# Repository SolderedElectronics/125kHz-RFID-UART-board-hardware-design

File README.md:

# 125kHz RFID tag reader UART board Hardware Design

## About the Product

|  |
| :----------------------------------------------------------: |
| [Buy 125kHz RFID tag reader UART board](https://www.solde.red/333154) |

RFID is a type of communication in which information is transmitted wirelessly (Wikipedia article). Today, it is becoming increasingly popular and can be found in numerous and various cards: driving licenses, access control to buildings, public transportation, etc.

RFID readers come in many forms and variants. This reader, from our production, enables easy connection to a microcontroller, thereby opening up possibilities for developing various projects based on RFID technology. The breakout comes in two versions, and depending on the version, it is programmed and ready for communication via pins on the board. It has a switch for changing the data transfer speed (baud rate) as well as a connector for connecting the antenna that comes with the breakout.

---

## Repository Contents

This repository contains all design files for 125kHz RFID tag reader UART board, organized as follows:

- **`CAD` folder**: Contains KiCAD design files, including:
  - Schematics
  - PCB layout
  - Panel PCB layout
  - Source 3D files in Fusion360, if any
  - All files are sorted by version with a detailed change log.
- **`OUTPUTS` folder**: Includes all production-ready files, such as:
  - Bill of Materials (BOM) and interactive BOM (iBOM)
  - PDF versions of schematics
  - 3D `.step` file of the board
  - 3D-printable models
  - Gerber files for PCB manufacturing
  - Image of the pinout of the board
  - Product image
  - Compliance, legal and generic sales documents

Refer to the `Change Log` in the CAD folder for details about updates between versions.

---

## Learn More About the Product

Beyond the repository, explore the following resources:

### Soldered Verify

The **Soldered Verify** system ensures every board you purchase from Soldered is fully functional. It also provides access to exclusive test data for your product. To get started, find the unique Soldered Verify ID on your product's packaging and enter the ID on the [Soldered Verify page](https://soldered.com/verify/) to access test results and additional product details.

### Soldered Community

Soldered Community is your go-to place for technical support. Our engineers track and answer all questions posted there, and it’s a great space for the maker community. Get answers to your questions and solutions for your challenges at [Soldered Community](https://soldered.com/community).

### solde.red

solde.red is an ultimate URL shortener and information hub. Access it by typing solde.red/ followed by your product SKU, e.g., [solde.red/333000](https://solde.red/333000), to find getting-started guides, datasheets, open-source hardware and software files, certifications, images, pinouts, and more. Read more about the shortener [here](https://solde.red/info/).

---

## Contributing

Contributions are welcome! Here’s how you can get involved:

- Submit pull requests to enhance the design or fix issues.
- Report bugs or problems by opening an issue.

We encourage community collaboration to make this product even better.

---

## About Soldered

[Soldered for Makers](https://soldered.com) specializes in designing and manufacturing electronic products tailored for enthusiasts, ranging from hobbyists to professionals. Our portfolio includes electronic boards, sensors, and actuators that are widely utilized in fields such as microelectronics, mechatronics, robotics, programming, and IoT. Every product we offer is designed in-house and built upon open-source hardware and software platforms. Proudly certified and manufactured within the European Union, our catalog likely includes the product you need for your project.

We complement these products with comprehensive tutorials and manuals, product descriptions, schematics, programming codes, and project examples. Our round-the-clock [customer and technical support](https://soldered.com/community) is available for all our products, irrespective of the sales channel. Soldered’s success and services reflect our maker community’s unwavering [trust](https://www.trustpilot.com/review/soldered.com), for which we are deeply grateful. Join our community and create using Soldered products.

---

## License

All Soldered open-source hardware (OSH) is under The TAPR Open Hardware License. Read more in the LICENSE file located in this repository.

**Disclaimer:**

No warranty - all designs in this repository are distributed in the hope that they will be useful, but without any warranty. They are provided "AS IS", therefore without warranty of any kind, either expressed or implied. The entire quality and performance of what you do with the contents of this repository are your responsibility. In no event Soldered Electronics will be liable for your damages, or losses, including any general, special, incidental, or consequential damage arising out of the use or inability to use the contents of this repository. 

---

## Have fun!

Thank you for your support from your fellow makers at Soldered Electronics.

Happy Making!

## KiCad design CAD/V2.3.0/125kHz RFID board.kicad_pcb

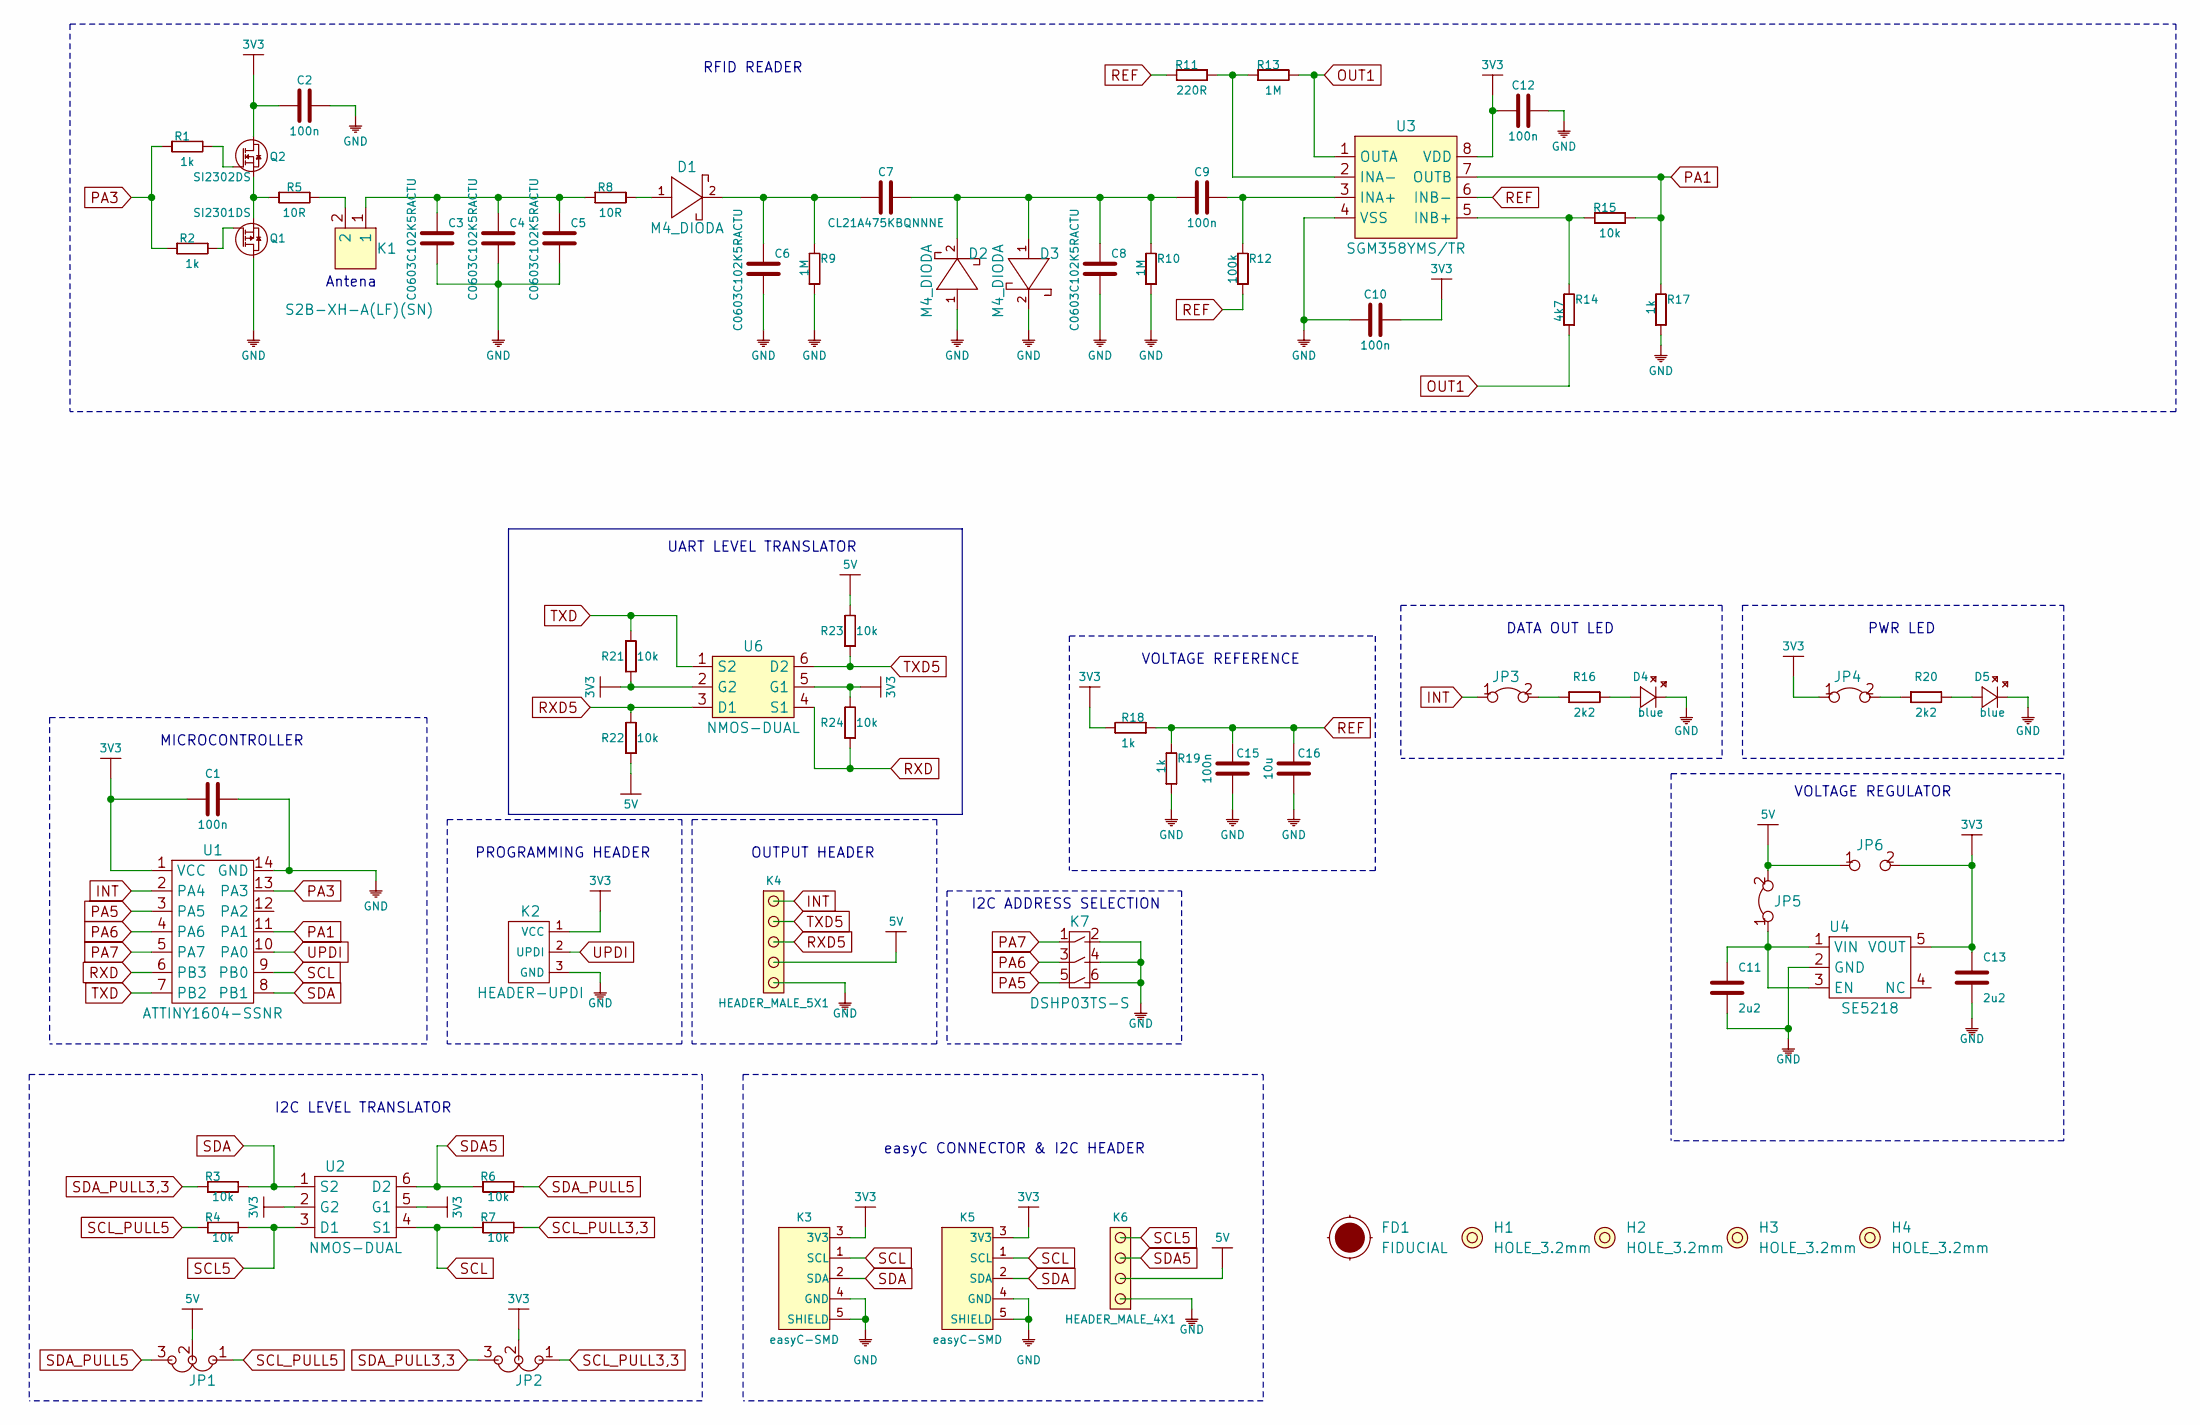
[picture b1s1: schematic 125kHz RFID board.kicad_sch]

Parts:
C1, C2, C9, C10, C12, C15: 100n; 0603C
C3, C4, C5, C6, C8: C0603C102K5RACTU; 0603C
C7: CL21A475KBQNNNE; 0805C
C11, C13: 2u2; 0603C
C16: 10u; 1206C
D1, D2, D3: M4_DIODA
D4, D5: blue; 0402LED
FD1: FIDUCIAL; FIDUCIAL_23
H1, H2, H3, H4: HOLE_3.2mm
JP1, JP2: SMD_JUMPER_3_PAD_TRACE
JP3, JP4: SMD-JUMPER-CONNECTED_TRACE_SLODERMASK
JP5: SMD-JUMPER-CONNECTED_TRACE_SOLDERMASK
JP6: SMD_JUMPER
K1: S2B-XH-A(LF)(SN)
K2: HEADER-UPDI
K3, K5: easyC-SMD; easyC-connector
K4: HEADER_MALE_5X1
K6: HEADER_MALE_4X1
K7: DSHP03TS-S
Q1: SI2301DS; SOT-23-3
Q2: SI2302DS; SOT-23-3
R1, R2, R17, R18, R19: 1k; 0603R
R3, R4, R6, R7, R15, R21, R22, R23, R24: 10k; 0603R
R5, R8: 10R; 0603R
R9, R10, R13: 1M; 0603R
R11: 220R; 0603R
R12: 100k; 0603R
R14: 4k7; 0603R
R16, R20: 2k2; 0402R
U1: ATTINY1604-SSNR; SOIC-14
U2, U6: NMOS-DUAL; SOT-363
U3: SGM358YMS/TR; MSOP-8
U4: SE5218; SOT-23-5

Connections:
3V3: C1.1, C2.1, C10.2, C12.1, C13.2, JP2.2, JP4.1, JP6.2, K2.1 (VCC), K3.3 (3V3), K5.3 (3V3), Q2.3 (D), R18.2, R21.1, R24.2, U1.1 (VCC), U2.2 (G2), U2.5 (G1), U3.8 (VDD), U4.5 (VOUT), U6.2 (G2), U6.5 (G1)
5V: JP1.2, JP5.2, JP6.1, K4.2, K6.2, R22.1, R23.2
GND: C1.2, C2.2, C3.1, C4.1, C5.1, C6.1, C8.1, C10.1, C11.1, C12.2, C13.1, C15.2, C16.2, D2.1 (A), D3.2 (K), D4.2 (K), D5.2 (K), K2.3 (GND), K3.4 (GND), K3.5 (SHIELD), K4.1, K5.4 (GND), K5.5 (SHIELD), K6.1, K7.2, K7.4, K7.6, Q1.3 (D), R9.1, R10.1, R17.1, R19.1, U1.14 (GND), U3.4 (VSS), U4.2 (GND)
INT: JP3.1, K4.5, U1.2 (PA4)
unnamed: C3.2, C4.2, C5.2, K1.1, R8.1
unnamed: C6.2, C7.1, D1.2 (K), R9.2
unnamed: C7.2, C8.2, C9.1, D2.2 (K), D3.1 (A), R10.2
unnamed: C9.2, R12.2, U3.3 (INA+)
unnamed: C11.2, JP5.1, U4.1 (VIN), U4.3 (EN)
unnamed: D1.1 (A), R8.2
unnamed: D4.1 (A), R16.2
unnamed: D5.1 (A), R20.2
unnamed: JP3.2, R16.1
unnamed: JP4.2, R20.1
unnamed: K1.2, R5.2
unnamed: Q1.1 (G), R2.2
unnamed: Q1.2 (S), Q2.2 (S), R5.1
unnamed: Q2.1 (G), R1.2
unnamed: R11.2, R13.1, U3.2 (INA-)
unnamed: R14.2, R15.1, U3.5 (INB+)
OUT1: R13.2, R14.1, U3.1 (OUTA)
PA1: R15.2, R17.2, U1.11 (PA1), U3.7 (OUTB)
PA3: R1.1, R2.1, U1.13 (PA3)
PA5: K7.5, U1.3 (PA5)
PA6: K7.3, U1.4 (PA6)
PA7: K7.1, U1.5 (PA7)
REF: C15.1, C16.1, R11.1, R12.1, R18.1, R19.2, U3.6 (INB-)
RXD: R24.1, U1.6 (PB3), U6.4 (S1)
RXD5: K4.3, R22.2, U6.3 (D1)
SCL: K3.1 (SCL), K5.1 (SCL), R7.1, U1.9 (PB0), U2.4 (S1)
SCL5: K6.4, R4.2, U2.3 (D1)
SCL_PULL3,3: JP2.1, R7.2
SCL_PULL5: JP1.1, R4.1
SDA: K3.2 (SDA), K5.2 (SDA), R3.2, U1.8 (PB1), U2.1 (S2)
SDA5: K6.3, R6.1, U2.6 (D2)
SDA_PULL3,3: JP2.3, R3.1
SDA_PULL5: JP1.3, R6.2
TXD: R21.2, U1.7 (PB2), U6.1 (S2)
TXD5: K4.4, R23.1, U6.6 (D2)
UPDI: K2.2 (UPDI), U1.10 (PA0)

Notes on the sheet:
I2C LEVEL TRANSLATOR
VOLTAGE REGULATOR
UART LEVEL TRANSLATOR
easyC CONNECTOR & I2C HEADER
OUTPUT HEADER
VOLTAGE REFERENCE
I2C ADDRESS SELECTION
DATA OUT LED
RFID READER
Antena
PROGRAMMING HEADER
MICROCONTROLLER
PWR LED

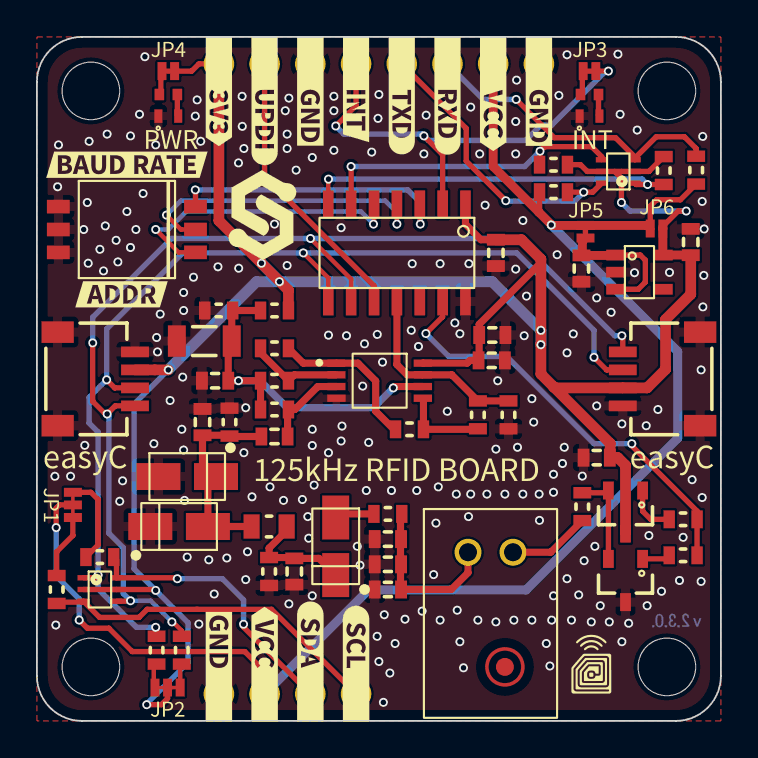
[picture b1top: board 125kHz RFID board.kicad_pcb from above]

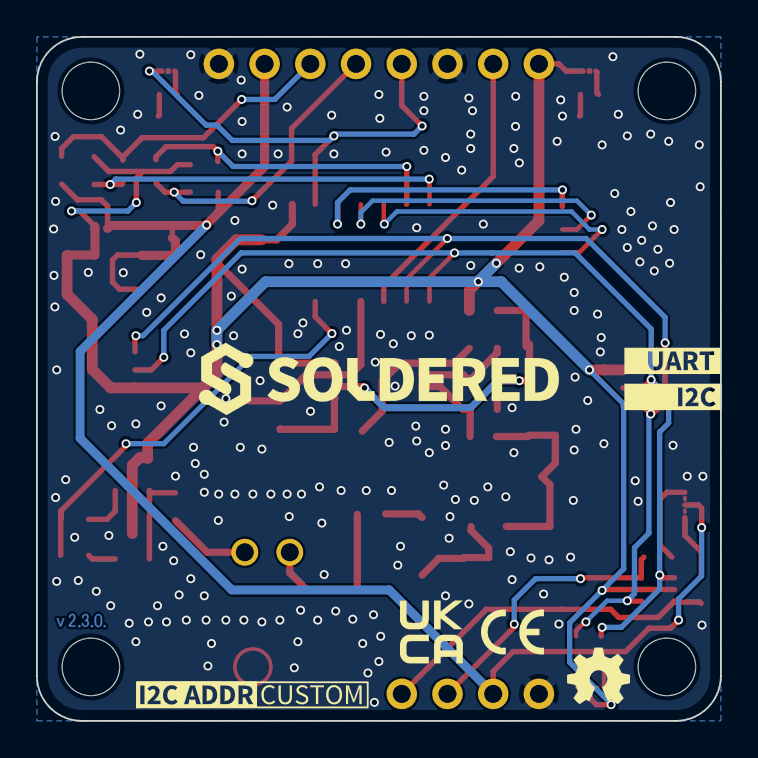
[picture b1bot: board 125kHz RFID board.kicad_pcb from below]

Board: 2 copper layers, 38.0 x 38.0 mm, 94 parts (4 on the bottom side), 40 nets.

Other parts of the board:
kibuzzard-64B62F4D: G***; kibuzzard-64B62F4D
kibuzzard-64B647F4: G***; kibuzzard-64B647F4
kibuzzard-64B64859: G***; kibuzzard-64B64859
kibuzzard-64004A7A: G***; kibuzzard-64004A7A
kibuzzard-64004A81: G***; kibuzzard-64004A81
kibuzzard-64004A90: G***; kibuzzard-64004A90
kibuzzard-64004AA4: G***; kibuzzard-64004AA4
kibuzzard-64004AB6: G***; kibuzzard-64004AB6
kibuzzard-64004AC9: G***; kibuzzard-64004AC9
kibuzzard-64004B51: G***; kibuzzard-64004B51
kibuzzard-64004B59: G***; kibuzzard-64004B59
kibuzzard-64004B65: G***; kibuzzard-64004B65
kibuzzard-64004B80: G***; kibuzzard-64004B80
kibuzzard-64004B92: G***; kibuzzard-64004B92
kibuzzard-64004BB0: G***; kibuzzard-64004BB0
kibuzzard-64004BB9: G***; kibuzzard-64004BB9
kibuzzard-64004D4D: G***; kibuzzard-64004D4D
kibuzzard-64004D5C: G***; kibuzzard-64004D5C
kibuzzard-64004D9E: G***; kibuzzard-64004D9E
kibuzzard-64004D69: G***; kibuzzard-64004D69
kibuzzard-64004D75: G***; kibuzzard-64004D75
kibuzzard-64004D85: G***; kibuzzard-64004D85
kibuzzard-64004D93: G***; kibuzzard-64004D93
kibuzzard-64004DB0: G***; kibuzzard-64004DB0
kibuzzard-64004EBC: G***; kibuzzard-64004EBC

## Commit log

2022-08-06 Updating open source files.
